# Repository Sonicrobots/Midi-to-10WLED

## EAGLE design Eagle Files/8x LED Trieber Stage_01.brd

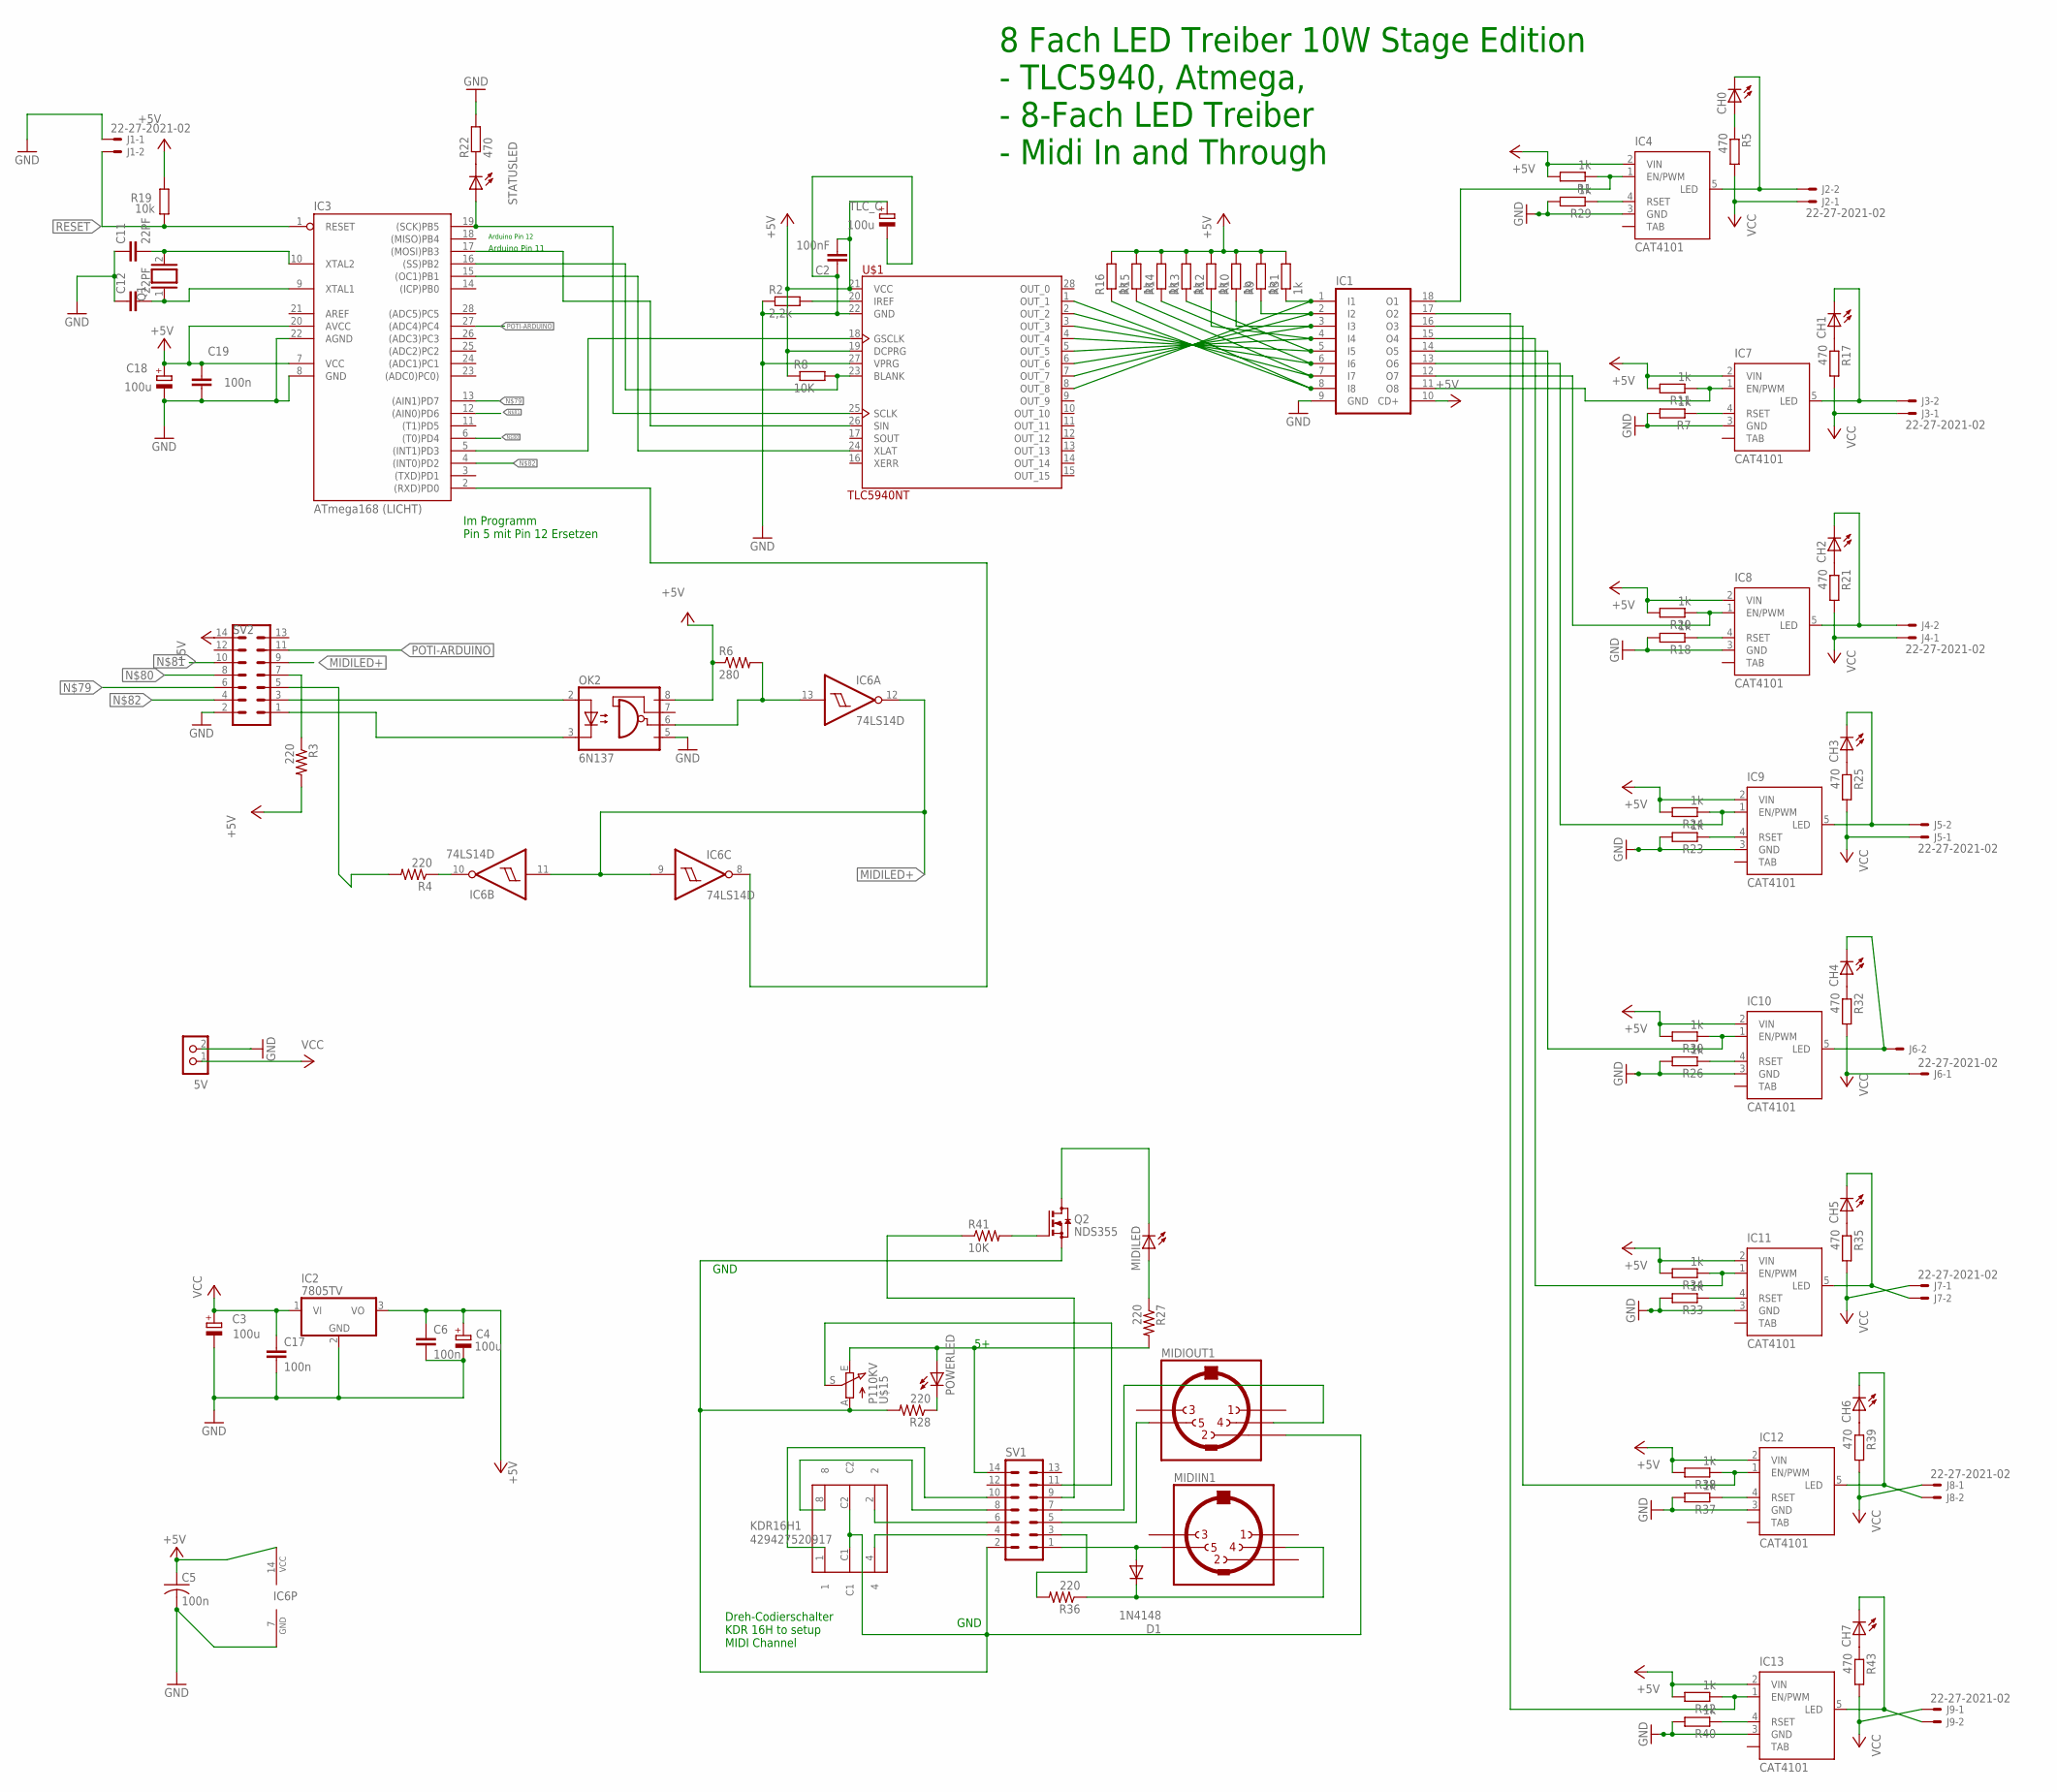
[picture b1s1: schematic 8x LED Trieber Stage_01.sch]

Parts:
5V: 5V; TERMINAL_BLOCK_2P_5
C2: 100nF; C0805
C3, C4, C18: 100u; E2,5-6
C5: 100n; C0805
C6, C17, C19: 100n; C0805K
C11, C12: 22PF; C0805
CH0, CH1, CH2, CH3, CH4, CH5, CH6, CH7: LED3MM
D1: 1N4148; D-7.5
IC1: IC_ULN2803AN; DIL18
IC2: 7805TV; TO220V
IC3: ATmega168 (LICHT); DIL28-3
IC4, IC7, IC8, IC9, IC10, IC11, IC12, IC13: CAT4101; TO263_5
IC6: 74LS14D; SO14
J1, J2, J3, J4, J5, J6, J7, J8, J9: 22-27-2021-02; 6410-02
KDR16H1: 429427520917
MIDIIN1: MAB5SH
MIDILED: LED3MM
MIDIOUT1: MAB5SH
OK2: 6N137; DIL08; MPN 6N137
POWERLED: LED3MM
Q1: XTAL/S; QS
Q2: NDS355; SOT23
R1, R7, R9, R10, R11, R12, R13, R14, R15, R16, R18, R20, R23, R24, R26, R29, R30, R31, R33, R34, R37, R38, R40, R42: 1k; R0805W
R2: 2,2k; R0805
R3, R4, R28, R36: 220; R0805
R5, R17, R21, R22, R25, R32, R35, R39, R43: 470; M0805
R6: 280; R0805
R8, R41: 10K; R0805
R19: 10k; R0805
R27: 220; R0805W
STATUSLED: LED3MM
SV1, SV2: ML14
TLC_C: 100u; E2,5-6
U$1: TLC5940NT; DIP-28
U$15: P110KV; POT-P110KV

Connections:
+5V: C2.2, C4.+, C5.1, C6.1, C18.+, C19.1, IC1.10 (CD+), IC2.3 (VO), IC3.7 (VCC), IC3.20 (AVCC), IC4.2 (VIN), IC6.14 (VCC), IC7.2 (VIN), IC8.2 (VIN), IC9.2 (VIN), IC10.2 (VIN), IC11.2 (VIN), IC12.2 (VIN), IC13.2 (VIN), OK2.8 (VCC), R1.2, R3.2, R6.1, R8.1, R9.2, R10.2, R11.2, R12.2, R13.2, R14.2, R15.2, R16.2, R19.2, R20.2, R24.2, R30.2, R31.2, R34.2, R38.2, R42.2, SV2.14, TLC_C.+, U$1.19 (DCPRG), U$1.21 (VCC)
GND: 5V.2, C2.1, C3.-, C4.-, C5.2, C6.2, C11.1, C12.1, C17.2, C18.-, C19.2, IC1.9 (GND), IC2.2 (GND), IC3.8 (GND), IC3.22 (AGND), IC4.3 (GND), IC6.7 (GND), IC7.3 (GND), IC8.3 (GND), IC9.3 (GND), IC10.3 (GND), IC11.3 (GND), IC12.3 (GND), IC13.3 (GND), J1.1, OK2.5 (GND), R2.1, R7.2, R18.2, R22.2, R23.2, R26.2, R29.2, R33.2, R37.2, R40.2, SV2.2, TLC_C.-, U$1.22 (GND), U$1.27 (VPRG)
MIDI-2: IC3.2 ((RXD)PD0), IC6.8 (O)
MIDILED+: IC6.9 (I), IC6.11 (I), IC6.12 (O), SV2.9
MIDILED+1: MIDILED.K (C), Q2.3 (D)
MIDI_IN2: R41.1, SV1.9
unnamed: OK2.3 (C), SV2.1
unnamed: IC6.13 (I), OK2.6 (VO), R6.2
unnamed: IC1.1 (I1), R31.1, U$1.8 (OUT_8)
unnamed: IC3.19 ((SCK)PB5), STATUSLED.A, U$1.25 (SCLK)
unnamed: IC1.2 (I2), R9.1, U$1.7 (OUT_7)
unnamed: IC1.3 (I3), R10.1, U$1.6 (OUT_6)
unnamed: IC1.4 (I4), R12.1, U$1.5 (OUT_5)
unnamed: IC3.17 ((MOSI)PB3), U$1.26 (SIN)
unnamed: IC3.16 ((SS)PB2), R8.2, U$1.23 (BLANK)
unnamed: IC7.4 (RSET), R7.1
unnamed: IC1.5 (I5), R13.1, U$1.4 (OUT_4)
unnamed: IC1.6 (I6), R14.1, U$1.3 (OUT_3)
unnamed: IC1.7 (I7), R15.1, U$1.2 (OUT_2)
unnamed: IC3.15 ((OC1)PB1), U$1.24 (XLAT)
unnamed: IC1.11 (O8), IC7.1 (EN/PWM), R11.1
unnamed: IC3.5 ((INT1)PD3), U$1.18 (GSCLK)
unnamed: IC1.8 (I8), R16.1, U$1.1 (OUT_1)
unnamed: D1.A, MIDIIN1.5, SV1.1
unnamed: R2.2, U$1.20 (IREF)
unnamed: KDR16H1.1, SV1.10
unnamed: C12.2, IC3.9 (XTAL1), Q1.1
unnamed: MIDILED.A, R27.1
unnamed: CH1.K (C), IC7.5 (LED), J3.2
unnamed: C11.2, IC3.10 (XTAL2), Q1.2
unnamed: R3.1, SV2.7
unnamed: R22.1, STATUSLED.K (C)
unnamed: IC4.4 (RSET), R29.1
unnamed: CH0.A, R5.1
unnamed: IC1.18 (O1), IC4.1 (EN/PWM), R1.1
unnamed: IC6.10 (O), R4.1
unnamed: R4.2, SV2.5
unnamed: SV1.11, U$15.S
unnamed: D1.C, MIDIIN1.4, R36.1
unnamed: CH0.K (C), IC4.5 (LED), J2.2
unnamed: POWERLED.K (C), R28.1
unnamed: CH1.A, R17.1
unnamed: IC8.4 (RSET), R18.1
unnamed: IC1.12 (O7), IC8.1 (EN/PWM), R20.1
unnamed: CH2.K (C), IC8.5 (LED), J4.2
unnamed: MIDIOUT1.5, SV1.5
unnamed: CH2.A, R21.1
unnamed: IC9.4 (RSET), R23.1
unnamed: IC1.13 (O6), IC9.1 (EN/PWM), R24.1
unnamed: OK2.2 (A), SV2.3
unnamed: CH3.K (C), IC9.5 (LED), J5.2
unnamed: MIDIOUT1.4, SV1.7
unnamed: CH3.A, R25.1
unnamed: IC10.4 (RSET), R26.1
unnamed: IC1.14 (O5), IC10.1 (EN/PWM), R30.1
unnamed: CH4.K (C), IC10.5 (LED), J6.2
unnamed: CH4.A, R32.1
unnamed: IC11.4 (RSET), R33.1
unnamed: KDR16H1.4, SV1.4
unnamed: IC1.15 (O4), IC11.1 (EN/PWM), R34.1
unnamed: KDR16H1.8, SV1.8
unnamed: KDR16H1.2, SV1.6
unnamed: CH5.K (C), IC11.5 (LED), J7.2
unnamed: CH5.A, R35.1
unnamed: POWERLED.A, R27.2, SV1.14, U$15.E
unnamed: IC12.4 (RSET), R37.1
unnamed: IC1.16 (O3), IC12.1 (EN/PWM), R38.1
unnamed: R36.2, SV1.3
unnamed: CH6.K (C), IC12.5 (LED), J8.2
unnamed: CH6.A, R39.1
unnamed: Q2.1 (G), R41.2
unnamed: KDR16H1.C1, KDR16H1.C2, MIDIOUT1.2, Q2.2 (S), R28.2, SV1.2, U$15.A
unnamed: IC13.4 (RSET), R40.1
unnamed: IC1.17 (O2), IC13.1 (EN/PWM), R42.1
unnamed: IC3.13 ((AIN1)PD7), SV2.6
unnamed: IC3.6 ((T0)PD4), SV2.8
unnamed: IC3.12 ((AIN0)PD6), SV2.10
unnamed: IC3.4 ((INT0)PD2), SV2.4
unnamed: CH7.K (C), IC13.5 (LED), J9.2
unnamed: CH7.A, R43.1
POTI-ARDUINO: IC3.27 ((ADC4)PC4), SV2.11
RESET: IC3.1 (RESET), J1.2, R19.1
VCC: 5V.1, C3.+, C17.1, IC2.1 (VI), J2.1, J3.1, J4.1, J5.1, J6.1, J7.1, J8.1, J9.1, R5.2, R17.2, R21.2, R25.2, R32.2, R35.2, R39.2, R43.2

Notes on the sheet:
8 Fach LED Treiber 10W Stage Edition - TLC5940, Atmega, - 8-Fach LED Treiber - Midi In and Through
Arduino Pin 12
Arduino Pin 11
Dreh-Codierschalter KDR 16H to setup MIDI Channel
GND
Im Programm Pin 5 mit Pin 12 Ersetzen

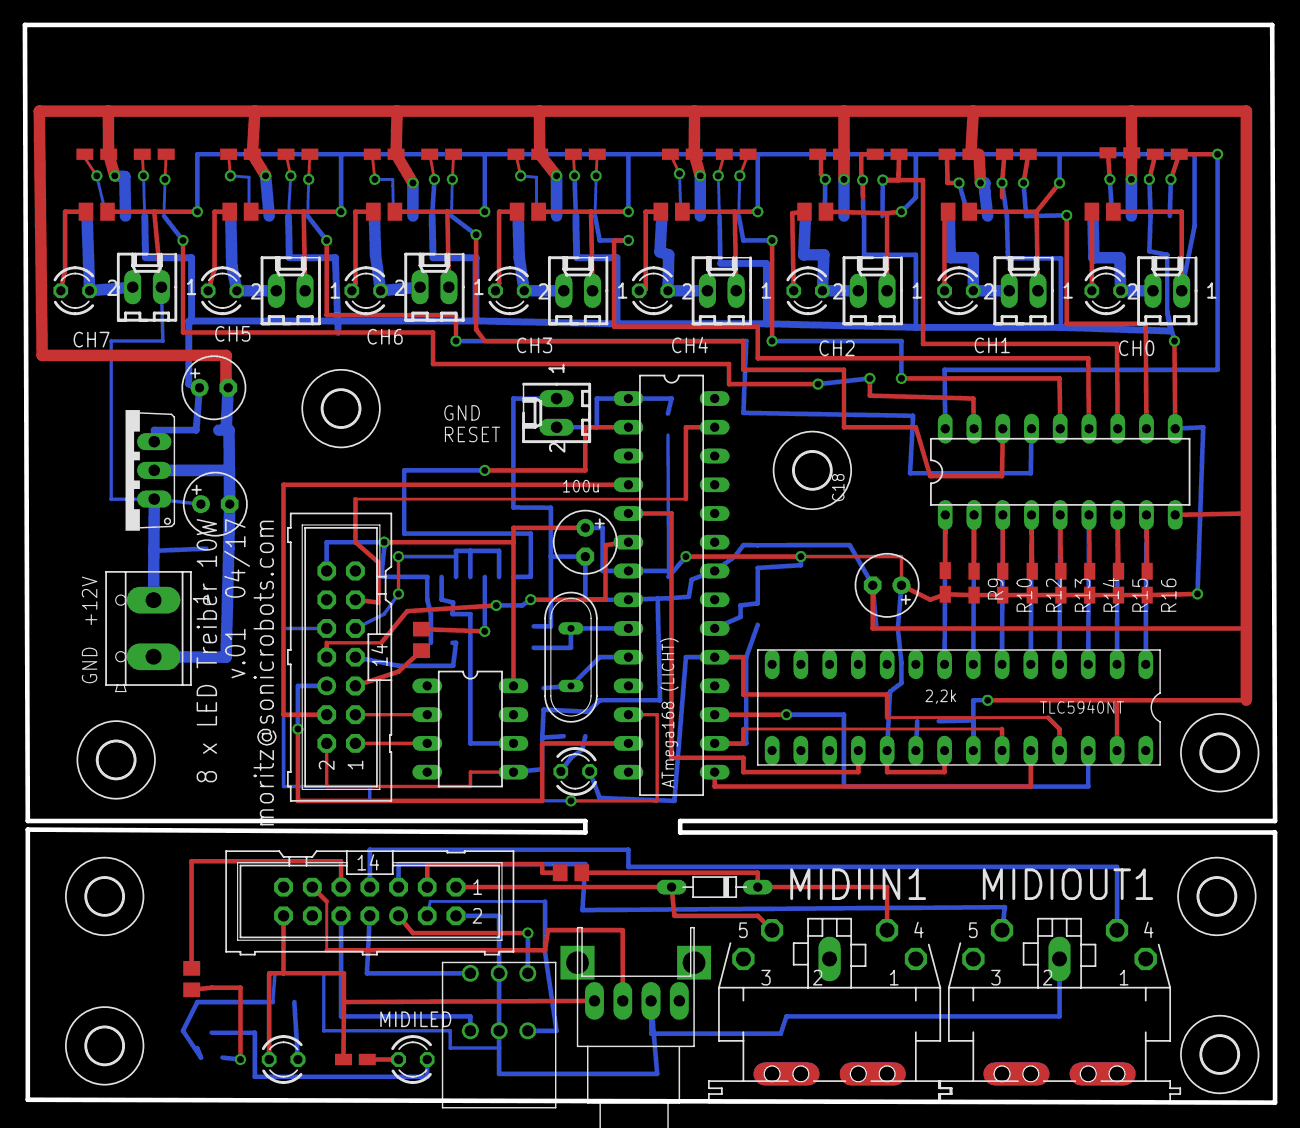
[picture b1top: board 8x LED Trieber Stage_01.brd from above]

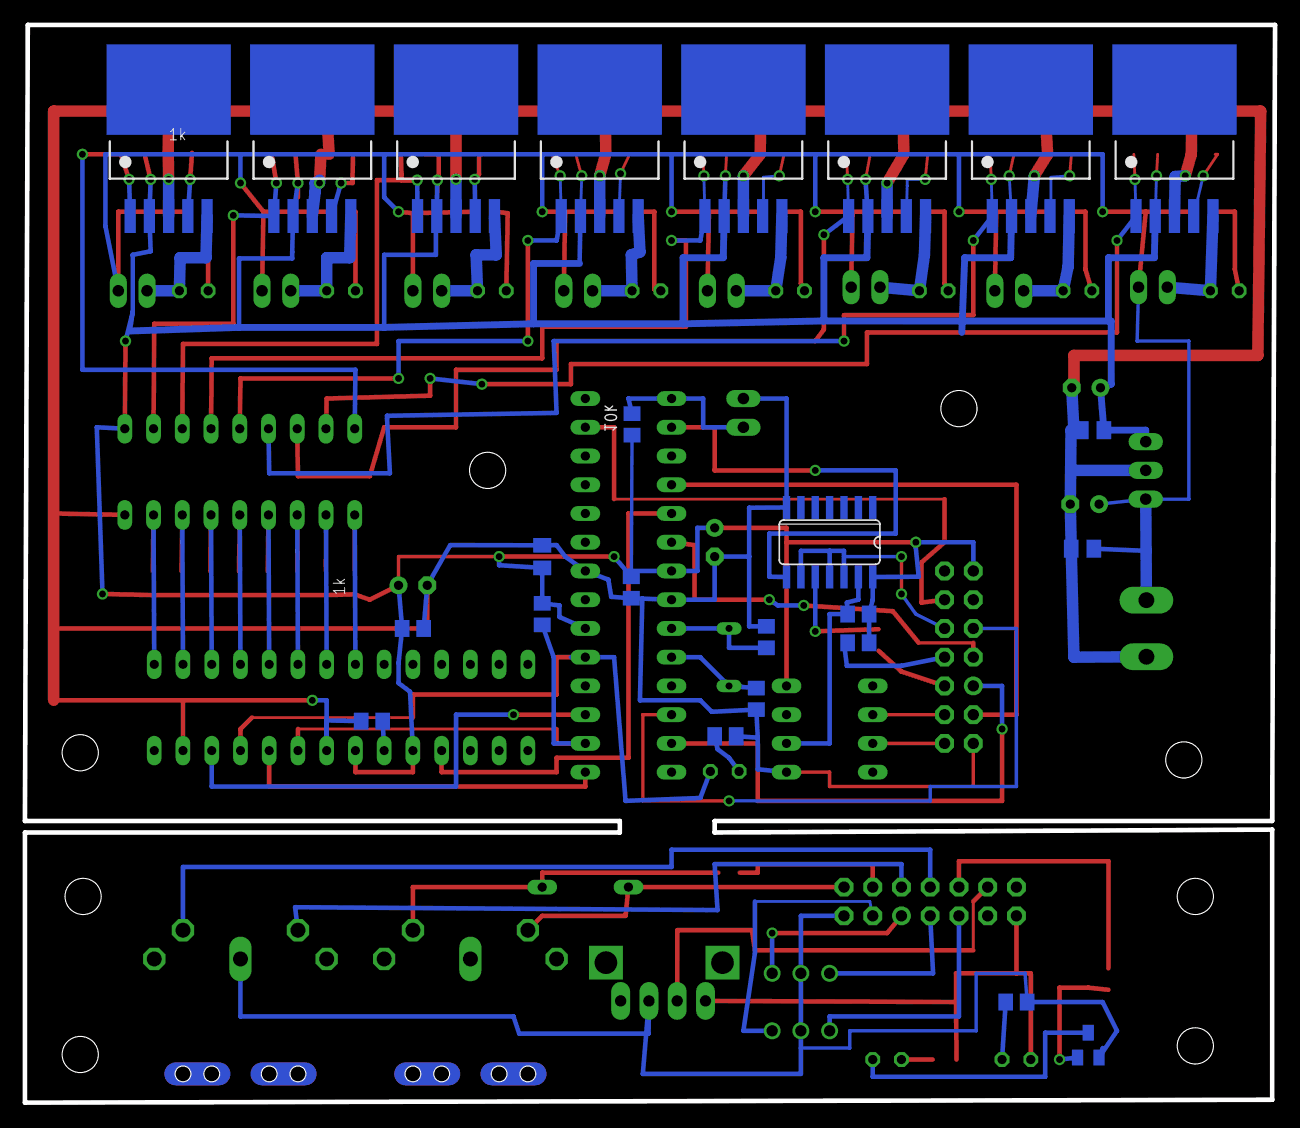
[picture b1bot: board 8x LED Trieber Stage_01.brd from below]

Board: 2 copper layers, 110.5 x 95.2 mm, 106 parts (24 on the bottom side), 83 nets.

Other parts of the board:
U$2, U$3, U$4, U$5, U$6, U$7, U$8, U$9: 3,2

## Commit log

2017-04-22 Eagle Files v01 added
2017-04-22 Arduino Files added
2017-05-06 Arduino and Eagle Fixes
    Channels in Arduino Coded fixed, Annotations in eagle added

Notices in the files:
parts and their libraries:
tlc5940: Hereby placed under Public Domain
Eagle_Wuerth_Elektronik_Switch: Copyright: Würth Elektronik
